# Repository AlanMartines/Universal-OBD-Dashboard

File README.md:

# Universal-OBD-Dashboard

Desenvolvido por **Alan Martines** · mantido pela **[Eletro Info Tecnologia](https://www.eletroinfotecnologia.com.br/)**.
<br clear="left">

Universal-OBD-Dashboard é uma plataforma de telemetria automotiva de código aberto projetada para Android e Android Auto. O projeto utiliza adaptadores OBD2 (Bluetooth SPP / chip duplo PIC18F25K80) para coletar, calcular e exibir dados do veículo com alta fidelidade, funcionando de forma 100% agnóstica via arquivos de perfil JSON.

*English summary: [README.en.md](README.en.md).*

Os seis temas do painel no modo noite, em cada aba do rodapé (dados do simulador):

| Tema | Estrada | Motor | Viagem | Dinâmica |
|---|---|---|---|---|
| **Minimal** |  |  |  |  |
| **Cápsula** |  |  |  |  |
| **HUD** |  |  |  |  |
| **Pista** |  |  |  |  |
| **Clássico** |  |  |  |  |
| **Horizonte** |  |  |  |  |

## Destaques
- **Compatibilidade com Android Auto**: Interface nativa baseada na AndroidX Car App Library. Instalado por APK, o app não aparece no carro a partir do Android Auto 17.7 ([detalhes](docs/android-auto.md#no-carro-apk-fora-da-play-store)).
- **Motor em Segundo Plano**: Coleta ininterrupta de dados e diagnóstico com tela do celular bloqueada (Foreground Service).
- **Caixa Preta de Viagens**: Registro contínuo em banco de dados SQLite local (Trip Computer e logs de DTCs).
- **Perfis Customizáveis**: Configure fórmulas, limites de RPM/temperatura e PIDs específicos por montadora sem alterar o código-fonte.
- **Perfil Uno Vivace Incluso**: Mapeamento completo para Fiat Uno Vivace 1.0 Flex (ECU Magneti Marelli IAW 7GF).

## Hardware Recomendado
- Adaptador OBD2 Bluetooth (SPP) compatível com ELM327, inclusive os clones "v1.5" com PIC18F25K80, usados no desenvolvimento. Adaptadores com chip STN (OBDLink) também funcionam. *Ajustes → Console da rede → Identificar adaptador* mostra o que é o seu.
- Dispositivo Android 8.0+ compatível com Android Auto.
- O app **só faz consultas** ao carro: leituras do modo 01, códigos de falha, identificação e comandos do próprio adaptador. Nada é escrito na ECU.

## Arquitetura

```
 ┌──────────── ObdForegroundService (FGS connectedDevice|location + Partial WakeLock) ────────────┐
 │                                                                                                 │
 │  BluetoothSerialManager ──► CommandQueue (EDF, 1 comando em voo) ──► TelemetryHub (StateFlow)   │
 │        SPP/RFCOMM             alta 100 ms │ média 1,5 s │ sentinela 10 s        │               │
 │                                                                                 ▼               │
 │  GPS (Google ou nativo) ────────────────────────────────────────────► TelemetryEngine (250 ms) │
 │                                                    consumo · marcha · alertas · energia         │
 │                                                                                 │               │
 │                                                     Room: trips · telemetry_log (2 s) · DTCs    │
 └─────────────────────────────────────────────────────────────────────────────────────────────────┘
          ▲ AutoDisconnectReceiver (ACL)       TelemetryHub ──► TelemetryScreen (Android Auto)
          ▲ DashboardSession (Android Auto)                └──► MainActivity (WebView assets/web)
```

| Pacote | Arquivo | Responsabilidade |
|---|---|---|
| `obd` | `ProfileParser.kt` | Modelo do perfil JSON, validação e **avaliador de fórmulas** (compila para AST uma vez) |
| `obd` | `ElmProtocol.kt` | Parser de respostas ELM327 (single/multi-frame ISO-TP, erros) e decodificador de DTC |
| `obd` | `CommandQueue.kt` | Escalonador das três esteiras sobre o socket SPP |
| `obd` | `BluetoothSerialManager.kt` | Socket RFCOMM, leitura até o prompt `>` e timeouts |
| `telemetry` | `TelemetryHub.kt` / `TelemetryEngine.kt` | Estado compartilhado, consumo, indicador de marcha, alertas, acumulador de viagem |
| `service` | `ObdForegroundService.kt` | Ciclo de vida, reconexão, GPS, máquina de estados de energia, gravação Room |
| `service` | `AutoDisconnectReceiver.kt` | Início/fim automáticos por eventos Bluetooth |
| `car` | `DashboardCarAppService.kt` / `TelemetryScreen.kt` | Android Auto (`GridTemplate`) |
| `db` | `AppDatabase.kt` / `TripDao.kt` / `TelemetryEntity.kt` | Caixa preta SQLite (viagens, telemetria, falhas, abastecimentos, respostas da IA) |
| `bridge` | `AppBridge.kt`, `HistoryBridge.kt`, `FuelBridge.kt`, `DiagnosticsBridge.kt`, `AiBridge.kt` | Pontes JavaScript da tela, uma por assunto (contrato conferido por `BridgeContractTest`) |
| `fuel` | `FuelLog.kt` / `FuelCalibration.kt` | Consumo real entre tanques cheios, mistura etanol/gasolina, calibração |
| `ai` | `AiClient.kt`, `DtcPrompt.kt`, `TripDigest.kt`, `HistoryContext.kt` | Assistente IA opcional (só agregados saem do celular) |
| `backup` | `BackupArchive.kt` / `BackupManager.kt` | Backup completo (.zip) e restauração |
| `diagnostics` | `CanListener.kt`, `AdapterIdentify.kt`, `DiagnosticRecorder.kt` | Console da rede, identificação do adaptador e gravação de diagnóstico |

A tela (`assets/web`) é dividida em `app-core.js` (ponte e utilitários) … `app-main.js` (inicialização), carregados em ordem pelo `index.html`; `WebAssetsTest` confere ids e nomes repetidos.

### Escalonador (CommandQueue)

Cada comando tem `próximo_envio = último_envio + intervalo_da_esteira`. A cada iteração é enviado o comando vencido com o prazo mais antigo (*Earliest-Deadline-First*); empates favorecem a esteira de maior prioridade. Nunca há escrita antes do prompt `>` da resposta anterior, o que evita o `BUFFER FULL` do ELM327.

Um ELM327 via SPP responde tipicamente 10–25 requisições/s. Com 4 PIDs a cada 100 ms (40 req/s) a esteira de alta frequência roda "o mais rápido possível" e o EDF garante que média e sentinela não sofram inanição. Otimizações incluídas:

- `ATS0` (sem espaços) e sufixo de contagem de respostas (`010C1`, `append_response_count`), que faz o ELM devolver sem esperar o timeout;
- descoberta de PIDs suportados (`0100/0120/…`): PIDs ausentes são desativados ou trocados pelo `fallback_command` (ex.: tensão `0142` → `ATRV`);
- modo ocioso: com o veículo parado, as esteiras são desaceleradas (`idle_poll_multiplier`).

### Gerenciamento de energia

| Evento | Ação |
|---|---|
| ACL do adaptador/dispositivo-gatilho conecta | inicia o serviço |
| Sessão do Android Auto criada | inicia o serviço |
| Bluetooth cai e não reconecta (`reconnect_attempts`, padrão 6) | salva a viagem e encerra |
| Adaptador responde mas a ECU não (ignição ainda desligada) | espera até `ignition_wait_s` (5 min) antes de encerrar |
| ECU sem resposta por `ecu_silence_timeout_s` (ignição desligada com adaptador ainda energizado) | salva a viagem e encerra |
| OBD **e** GPS ≤ limiar pelo tempo de *Ajustes → Captura* (5, 15 ou 30 min, ou nunca; padrão 15) | notificação "Continuar / Encerrar" (também no Android Auto); polling e GPS em baixa potência |
| Sem resposta em `idle_confirm_timeout_s` | salva a viagem e encerra |

> **Adaptadores ELM327 são passivos**: o evento `ACL_CONNECTED` só ocorre quando o telefone abre o socket. Para início 100% automático, cadastre em *Ajustes → Dispositivos-gatilho* o nome Bluetooth da multimídia do carro ou use o Android Auto. No Android 12+ o sistema pode bloquear o início a partir de segundo plano; nesse caso aparece uma notificação "Toque para iniciar".

### Exportação de viagens

Na aba *Histórico*, cada viagem tem os botões **CSV** e **GPX**, que abrem o menu de compartilhamento do Android (Drive, e-mail, WhatsApp...).

| Formato | Conteúdo |
|---|---|
| CSV | Uma linha por amostra da caixa preta (2 s): `timestamp_ms`, `time_utc`, colunas fixas (rpm, velocidade OBD/GPS, TPS, MAP, temperaturas, tensão, trims, lambda, consumo, GPS) e uma coluna para cada saída extra do perfil. Vírgula como separador e ponto decimal. |
| GPX 1.1 | Trajeto com `<trkpt>` por amostra com GPS (novo segmento após 30 s sem fix), extensões `obd:speed_kmh`, `obd:rpm`, `obd:coolant_c`, `obd:throttle_pct` e `obd:fuel_lph`, e um `<wpt>` por falha (DTC) com o freeze frame. Abre no Google Earth, Strava, OsmAnd etc. |

O código fica em `export/TripExporter.kt` (Kotlin puro, testado na JVM) e `export/TripExportFiles.kt` (arquivo em `cache/exports`, apagado após 24 h).

### Gravação de diagnóstico

Para testes em veículos novos e para calibração, ative *Ajustes → Gravação de diagnóstico*. A partir da próxima captura, cada sessão gera um arquivo `diag_<data>_<perfil>.jsonl`, com uma linha JSON por evento:

| `type` | Conteúdo |
|---|---|
| `session` | versão do app, perfil, celular/Android, nomes do adaptador |
| `adapter` | versão do ELM, PIDs suportados e desativados |
| `elm` | `cmd`, resposta bruta `rx` (ou `err`), latência `ms` |
| `scan` | início/fim da varredura única da ECU (respostas nas linhas `elm`) |
| `snapshot` | 1×/s: leituras, métricas derivadas, GPS, estado de conexão/energia |
| `status`, `power`, `alert`, `dtcs`, `pid_status`, `error`, `stop` | eventos da sessão |

Em *Ajustes*, cada arquivo tem **Exportar .gz** (menu de compartilhar). Falhas fatais do app ficam em `crash_<data>.txt` na mesma lista. Ocupa cerca de 5–10 MB por hora (bem menos compactado).

### Assistente IA (opcional)

*Ajustes → Assistente IA* liga um botão **Explicar com IA** em cada código de falha, nas falhas ativas e no histórico. O app manda à IA o veículo, o motor/ECU, o código, a descrição do perfil e as leituras do momento da falha (rotação, velocidade, carga, temperatura), e mostra a resposta: significado, causas prováveis, gravidade e o que verificar.

- **Provedores:** qualquer API no formato OpenAI (`POST <endereço>/chat/completions`, chave em `Authorization: Bearer`).

  | Provedor | Endereço |
  |---|---|
  | OpenAI | `https://api.openai.com/v1/` |
  | Claude | `https://api.anthropic.com/v1/` |
  | Gemini | `https://generativelanguage.googleapis.com/v1beta/openai/` |
  | Personalizado | outro endereço `https://` (OpenRouter, Groq…) |

  Com a chave colada, **Atualizar modelos** busca na conta do provedor os modelos de texto que ela pode usar (`GET <endereço>/models`; na Claude, com os cabeçalhos `x-api-key` e `anthropic-version` da Anthropic). É só escolher na lista. O nome também pode ser digitado.
- **Privacidade:**
  - Nunca saem GPS, trajeto, horário, VIN nem o número da viagem. O lado nativo só aceita uma lista fechada de campos, e um teste garante isso.
  - Antes do primeiro envio, o app mostra o texto exato que vai sair. Depois disso, ele continua disponível em "O que foi enviado".
- **Analisar viagem:** o botão **Analisar com IA** de cada viagem envia um resumo calculado no celular, sem coordenadas, horário nem VIN. O resumo traz:
  - distância, tempos em movimento e parado;
  - faixas de velocidade e rotação e o tempo em cada marcha estimada;
  - consumo em até 8 trechos;
  - temperaturas, tensão e falhas.
- **Perguntar à IA** (aba Histórico): conversa sobre o carro. O contexto é montado no celular:
  - as 40 viagens mais recentes, com data sem horário;
  - os abastecimentos, sem nome do posto nem observações;
  - consumo real, gastos por mês e o ponto de equilíbrio etanol × gasolina;
  - as falhas registradas.
- **Confirmação:** antes do primeiro envio de cada tipo (falha, viagem, pergunta), o app mostra o texto e espera o **Enviar**.
- **Chave de API:**
  - Cifrada com AES-GCM, com a chave no Android Keystore do aparelho.
  - Aparece mascarada e não entra em exportações.
  - Em outro celular, um backup não a revela.
- **Custo e rede:** cada consulta usa créditos da sua conta no provedor. Sem internet, o botão avisa e o resto do app funciona igual.

### Telemetria remota (opcional)

*Ajustes → Telemetria remota* envia as leituras para um servidor próprio ([server/](server/README.md)). Fica desligada até você parear.

- **Pareamento:** no painel, crie o dispositivo e use o código de uso único no app. O app gera um identificador aleatório e não usa IMEI nem MAC.
- **O que sai:** só as leituras dos sensores, o horário, o número da viagem e os códigos de falha ativos. VIN não é enviado. O GPS tem opção própria, desligada por padrão.
- **Só de saída:** a resposta do servidor nunca vira comando para o adaptador ou o carro.
- **Sem sinal:** a telemetria continua na caixa preta do celular e sobe depois. O histórico anterior ao pareamento não é enviado.
- **Quando envia:** durante a captura, ou ao tocar em *Enviar agora*.
- **Painel do veículo:** durante a captura, o app também manda a última leitura para o painel web: uma por segundo com alguém olhando e uma a cada 10 s sem ninguém, para economizar dados. Essa leitura não fica guardada.
- **Segurança:** apenas `https://`, sem seguir redirecionamentos. O token fica cifrado no Android Keystore.

### Console da rede (escuta CAN)

*Ajustes → Console da rede* abre uma tela tipo terminal que escuta por 60 s o tráfego CAN dos pinos 6/14, somente ouvindo: o ELM327 fica em modo silencioso (`ATCSM1`) e só recebe comandos `AT`. Se o adaptador não aceitar o modo silencioso, a escuta é cancelada. Com *Velocidade: automática*, o app experimenta 500, 250, 125, 100, 83,3, 50 e 33,3 kbps por 4 s cada e escuta na que trouxe mais quadros. No fim, mostra um resumo por ID com os bytes que variaram.

**Identificar adaptador** (no mesmo console) envia só comandos internos do adaptador, nunca ao carro: `ATZ`, `ATI`, `AT@1`, `AT@2`, `ATPPS`, `ATCSM1`, `STI` e `ATRV`. Com as respostas, o app aponta clone de ELM327, chip STN (OBDLink) ou "nenhum sinal de clone". Um adaptador é clone quando declara uma versão que a Elm Electronics nunca lançou (como a v1.5) ou quando diz ser v1.4 ou mais nova sem conhecer `ATCSM`/`ATPPS`. O resultado fica em `diag_<data>_console-identificar.jsonl`.

Cada escuta gera `diag_<data>_console-escuta.jsonl`, com linhas `can` (`l` = quadro bruto, `ms` desde o início), `can_probe`, `can_summary` e `elm`. O arquivo aparece no histórico do console e na lista de arquivos de diagnóstico, com as opções ver, exportar .gz e apagar. Use com a captura encerrada e a ignição ligada.

Se o adaptador for um clone sem `ATCSM`, como o usado no desenvolvimento, a escuta pode ser feita fora do app com um Arduino Uno + MCP2515 em modo Listen-Only, que garante no hardware que nada é transmitido: veja [docs/can-escuta.md](docs/can-escuta.md).

### Continuidade da viagem

Depois de uma **desconexão automática** (ignição desligada, queda de Bluetooth, inatividade sem resposta, app reiniciado pelo sistema), uma captura que começa até **1 hora** depois (ajustável em *Ajustes → Captura*) **continua a mesma viagem**: mesmos totais no histórico, mesmo CSV/GPX e mesmo arquivo de diagnóstico (com um evento `resume`). Encerrar à mão (*Encerrar viagem* no app, na notificação ou no Android Auto, ou *Encerrar agora* na inatividade) faz a próxima captura começar uma viagem nova. A varredura de diagnóstico da ECU roda uma vez por dia por veículo, e *Ajustes → Pronto para viajar* lista as permissões e ajustes de bateria que mantêm a captura e o GPS em segundo plano.

### Painel de instrumentos

A aba **Painel** mostra os instrumentos em seis temas, trocados pelo botão no rodapé do painel: **Minimal** (barra de RPM no topo, marcha e velocidade grandes), **Cápsula** (velocímetro e conta-giros de arco na cor escolhida, verde ou vermelho, cápsula central com luzes, barras de combustível/temperatura e células), **HUD** (moldura neon com escalas na borda e estrada animada pela velocidade), **Pista** (conta-giros em setores com a marcha no miolo e luzes de troca), **Clássico** (dois mostradores redondos com aro metálico e ponteiro) e **Horizonte** (arco largo de RPM com a velocidade no centro). Cada tema tem modo dia/noite (automático pelo tema do Android ou pelo horário) e três telas de seis campos (**Estrada**, **Motor**, **Viagem**), trocadas por toque, por deslize ou sozinhas (Viagem quando o carro para). A quarta aba, **Dinâmica**, ocupa a tela toda com o câmbio (P parado, D andando, R de ré), o inclinômetro lateral e frontal, a força G, a bússola com o horizonte, a curva (direção e giro) e o ambiente (altitude e pressão); usa o LSM6DS3 e o magnetômetro da placa do ESP32, cruzados com o GPS do celular (parado, o rumo vem do magnetômetro do ESP32, da bússola do próprio celular ou da média das duas quando concordam), e tem os botões **Zerar nível** e **Calibrar frente**. Limites, faixas térmicas, relações de marcha e papéis vêm do perfil JSON, então o painel serve para qualquer veículo.

Com o celular **na horizontal** e o Painel aberto, o app entra em tela cheia; durante a captura, com o Painel aberto, a tela fica ligada. O painel anterior, com todos os sensores, alertas e falhas em lista, continua na aba **Detalhes**. Para avaliar os temas fora do app (simulador ou trecho de viagem real), veja [tools/painel-preview](tools/painel-preview/README.md).

### Detalhes: falhas e monitores de prontidão

A aba **Detalhes** mostra as falhas ativas e os **monitores de prontidão** da ECU: os autodiagnósticos que ela roda sozinha ao dirigir (catalisador, sonda, sistema de combustível, falha de ignição…), vindos dos bytes B–D do PID `0101`. "Em teste" é normal depois de desligar a bateria ou apagar códigos.

Quando surge uma falha nova, o app lê uma vez o **congelamento de quadro gravado pela própria ECU** (modo 02). O resultado aparece no histórico de falhas e entra no "Explicar com IA".

### Abastecimentos

A aba **Abastecimentos** registra cada parada no posto: data e hora, hodômetro, litros, valor pago (ou preço por litro), combustível (gasolina, aditivada/premium, etanol ou mistura), se foi tanque cheio e o posto. Com dois **tanques cheios** com hodômetro, o app mostra o **consumo real** (litros colocados ÷ km rodados), o **custo por km**, o **gasto do mês** e, para cada intervalo, quanto o próprio app tinha estimado, como conferência da calibração. Com tanques cheios de etanol e de gasolina, mostra a partir de que preço o **etanol compensa neste carro**. Registrar um tanque cheio na hora também acerta o nível do tanque e o hodômetro do app.

O card **Calibração do consumo** compara, em cada intervalo entre tanques cheios, os litros reais com o que o app estimou. A estimativa é a integral do consumo gravado no período. Com 3 ou mais intervalos parecidos, o card sugere um fator de correção, que se aplica com um toque e vale por veículo. Intervalos com diferença acima de 25% ficam de fora, por exemplo tanque não completado ou % de etanol errado.

**Etanol da bomba no tanque** (em Ajustes) é só a parte do tanque que veio da bomba de etanol: 0% = só gasolina. O etanol anidro que a lei manda misturar na gasolina (32% na comum e aditivada desde agosto de 2026; 25% na premium) já está no combustível "gasolina" do perfil e não deve ser somado ali.

**Exportar CSV** compartilha todos os abastecimentos (`data_hora,hodometro_km,litros,valor_total,preco_litro,combustivel,etanol_pct,tanque_cheio,posto,observacao`); o mesmo formato pode ser importado de um arquivo (**Escolher arquivo .csv**) ou colado em **Importar**, com a opção de substituir todos os registros.

### Backup completo

*Ajustes → Backup completo* gera um `.zip` com o banco (viagens, telemetria, falhas, abastecimentos, respostas da IA), os ajustes e os perfis importados, para guardar ou levar para outro celular. **Restaurar backup** substitui tudo pelo conteúdo do arquivo, migrando o banco se o backup for de uma versão anterior, e recusa backups de versões mais novas. A chave de API da IA não entra no backup. Com esse CSV, `tools/trip-report --fuel-csv` calibra o consumo intervalo a intervalo.

## Perfis JSON

Passo a passo para criar o perfil de outro carro: [docs/criar-perfil.md](docs/criar-perfil.md).

Perfis embarcados ficam em `app/src/main/assets/profiles/`. Perfis importados pela tela *Ajustes* são gravados em `<filesDir>/profiles/` e têm precedência sobre os embarcados com o mesmo `profile_id`.

| Seção | Descrição |
|---|---|
| `init_commands` | Sequência AT enviada após conectar |
| `adapter` | Nomes Bluetooth, timeouts, `append_response_count`, `query_supported_pids` |
| `lanes` | `interval_ms`, `priority` e `throttle_when_idle` de cada esteira |
| `pids.<esteira>[]` | `command`, `formula` (bytes `A`..`Z`) **ou** `outputs[]` (com `hidden` para valores internos), `decoder` (`formula`/`dtc`/`elm_voltage`), `fallback_*` |
| `roles` | Associa papéis semânticos (rpm, speed, map, coolant_temp…) aos ids do perfil |
| `alerts[]` | `condition` (expressão sobre os ids), `level`, `message` com `{id}`, `sustain_ms`, `notify` |
| `thermal`, `dashboard` | Faixas térmicas e limites dos mostradores |
| `fuel` | Tanque, reserva, método (`speed_density`/`maf`), cilindrada, VE, combustíveis flex, corte em desaceleração |
| `shift_indicator` | Velocidades de troca econômica e, opcionalmente, km/h por 1000 RPM de cada marcha |
| `power_management` | Tempos de inatividade, silêncio da ECU e reconexão |

**Fórmulas e condições** aceitam `+ - * / %`, `& | ^ << >>`, comparações, `&& || !`, ternário `c ? a : b` e as funções `min max abs round floor ceil sqrt clamp signed8 signed16`. Nas condições de alerta também estão disponíveis `gps_speed`, `fuel_lph`, `fuel_kml`, `fuel_remaining_l`, `trip_distance_km`, `dtc_confirmed_count` e `dtc_pending_count`. Valor ausente vale `NaN`, então a condição é falsa e não há alerta com dado faltando.

### Perfil Fiat Uno Vivace (IAW 7GF)

É o primeiro carro mapeado, não uma regra para os demais. Cada veículo tem a sua pasta em [veiculos/](veiculos/README.md), e a ligação com ESP32 é específica de cada um.

- ISO 14230-4 KWP FAST pela linha K (pino 7), confirmado em viagem; `ATSP5` fixa esse protocolo, sem busca automática que transmitiria na CAN da carroceria; RPM 0–7000 com redline em 6250 RPM e marcha lenta de 815 ± 50 RPM;
- termostato 87 °C, eletroventilador 1ª 97 °C / 2ª 103 °C, crítico > 105 °C;
- troca econômica 1→2 aos 14,8 km/h, 2→3 aos 28,2, 3→4 aos 43,8 e 4→5 aos 61,4 km/h;
- tanque de 48 L, reserva entre 5,5 e 7,5 L (nível estimado por integração do consumo a partir do último "Tanque cheio");
- consumo por *speed-density* (a 7GF não tem MAF), com `volumetric_efficiency` 0,99 calibrada em três abastecimentos reais (consumo medido de 12,5–13,2 km/l na estrada com gasolina).

A luz **STOP** (pressão de óleo) do quadro é ligada direto ao pressostato e não é exposta via OBD. Especificações completas em [veiculos/fiat-uno-vivace-2012](veiculos/fiat-uno-vivace-2012/).

## Compilação

1. Android Studio com suporte ao AGP 9 (2026 ou mais recente), com o JDK 17 ou mais novo.
2. Abra a pasta do projeto; o Studio usa o Gradle do wrapper (9.x). O build é em Kotlin DSL (`*.gradle.kts`), com as versões em `gradle/libs.versions.toml`, e compila com o SDK 37 (`targetSdk` 36).
3. Pela linha de comando: `./gradlew :app:assembleDebug` gera `app/build/outputs/apk/debug/app-debug.apk` (requer `ANDROID_HOME` ou `sdk.dir` em `local.properties`).
4. Testes de unidade do núcleo (fórmulas, parser ELM, DTC, perfis): `./gradlew :app:testDebugUnitTest`.
   Inclui o **simulador de ELM327 em JVM** (`app/src/test/java/.../obd/sim/Elm327Simulator.kt`), que exercita a `CommandQueue` com os perfis reais, em tempo virtual, sem adaptador nem carro: protocolos CAN e K-Line, DTCs, ignição desligada, adaptador travado e clones limitados.

### Testar no Android Auto

O app usa a categoria `androidx.car.app.category.IOT`, porque não existe categoria de telemetria.

> **Limite do APK no carro:** a partir do Android Auto 17.7, a opção *Fontes desconhecidas* não libera mais apps da Car App Library instalados por APK. O app fica fora da lista do carro, mesmo com a opção ligada. Hoje, o Android Auto instalado por APK só funciona no simulador *Desktop Head Unit* (DHU) do computador. Detalhes e saídas em [docs/android-auto.md](docs/android-auto.md#no-carro-apk-fora-da-play-store).

O teste no DHU e o que conferir estão em [docs/android-auto.md](docs/android-auto.md). A tela também é testada automaticamente (`TelemetryScreenTest`).

### Integração contínua

Todo push no `master` e todo PR rodam no GitHub Actions ([ci.yml](.github/workflows/ci.yml)):
- `testDebugUnitTest`, `lintDebug` e `assembleDebug`. Os testes incluem Robolectric para a migração do banco, o backup e o Android Auto.
- Os testes das ferramentas `tools/trip-report` (inclusive a paridade do cálculo de consumo com o app) e `tools/can-capture`.
- O job **smoke**, que instala num emulador o APK otimizado pelo R8 (variante `smoke`: release com a chave de debug) e confere que o app abre sem travar.
- O job **servidor**, com os testes da `api` e do `web` contra um PostgreSQL descartável.
- O job **seguranca**:
  - procura segredos em todo o histórico com o gitleaks; os falsos positivos conferidos ficam no [.gitleaksignore](.gitleaksignore);
  - procura falhas conhecidas (altas e críticas, com correção disponível) nas dependências, nos Dockerfiles e nas imagens do painel com o Trivy.

O fluxo só tem permissão de leitura no repositório. As Actions são presas pelo hash do commit, e as ferramentas de segurança rodam pelas imagens oficiais presas por digest.

O Dependabot ([dependabot.yml](.github/dependabot.yml)) avisa toda semana sobre atualizações do Gradle, das Actions, do npm do painel e da imagem base do Node. O APK de debug e os relatórios de teste/lint ficam disponíveis como artefatos da execução.

O APK de debug é assinado com a chave fixa `app/debug.keystore` (versionada de propósito; senha `android`). Assim, APKs gerados pelo CI ou por qualquer máquina atualizam uns aos outros sem precisar desinstalar o app, o que apagaria viagens e ajustes.

### Releases

Ao enviar uma tag `vX.Y.Z`, o workflow [release.yml](.github/workflows/release.yml) roda os testes, gera o APK **assinado com a chave de release** e publica em *Releases* com as notas da seção `## [X.Y.Z]` do CHANGELOG. Tags `v0.*` saem como *pre-release*.

**Configuração (uma vez):**
1. No seu computador, rode `scripts/criar-chave-release.sh`. Ele cria `~/.android-keys/universal-obd-release.jks` (fora do repositório) e um `.base64.txt` dela.
2. Em *Settings → Secrets and variables → Actions*, cadastre `RELEASE_KEYSTORE_BASE64`, `RELEASE_STORE_PASSWORD`, `RELEASE_KEY_PASSWORD` e `RELEASE_KEY_ALIAS` (o script mostra os valores).
3. Apague o `.base64.txt` e faça **backup da chave e da senha**: sem elas não é possível publicar atualizações para quem já instalou o app.

**Publicar uma versão:**
1. No CHANGELOG, mova o conteúdo de `[Não lançado]` para `## [X.Y.Z] - AAAA-MM-DD` e atualize os links do rodapé.
2. Em `app/build.gradle.kts`, ajuste `versionName = "X.Y.Z"` e incremente `versionCode`.
3. Commit (`chore: versão X.Y.Z`), depois `git tag vX.Y.Z` e `git push origin master vX.Y.Z`.

O workflow falha com uma mensagem clara se a tag não bater com `versionName`, se a seção do CHANGELOG não existir ou se os secrets não estiverem configurados.

Para assinar um release localmente, defina as mesmas variáveis (`RELEASE_STORE_FILE`, `RELEASE_STORE_PASSWORD`, `RELEASE_KEY_ALIAS`, `RELEASE_KEY_PASSWORD`) no ambiente ou em `~/.gradle/gradle.properties` e rode `./gradlew :app:assembleRelease`. Sem elas o Gradle gera `app-release-unsigned.apk`.

> O APK de release usa outra chave, então não atualiza um APK de debug instalado (nem o contrário): troque de um para o outro desinstalando antes.

## Versionamento

O projeto segue o [Versionamento Semântico](https://semver.org/lang/pt-BR/) (`MAJOR.MINOR.PATCH`) e as mudanças de cada versão ficam no [CHANGELOG.md](CHANGELOG.md).

- **MAJOR**: mudança incompatível no formato dos perfis JSON (`schema_version`) ou no banco Room sem migração.
- **MINOR**: novas funcionalidades, PIDs, perfis de veículo ou telas compatíveis.
- **PATCH**: correções de bugs e ajustes de calibração.

As tags usam o prefixo `v` (ex.: `v0.1.0`) e devem coincidir com `versionName` em `app/build.gradle.kts`. Enquanto a versão for `0.x`, o formato dos perfis ainda pode mudar.

Versão atual: **0.4.0**.

## Como contribuir

Relatos de problema, perfis de outros carros e pull requests são bem-vindos. As regras (somente consulta ao carro, cuidado com dados pessoais) e o passo a passo estão em [CONTRIBUTING.md](CONTRIBUTING.md).

## Licença
O código é distribuído sob a [licença MIT](LICENSE).

O nome **Eletro Info Tecnologia**, a logo e o emblema `[EI]` (ícone do app) são marcas da Eletro Info Tecnologia e **não** fazem parte da licença MIT. Quem publicar uma versão modificada do app deve usar outro nome e outro ícone.

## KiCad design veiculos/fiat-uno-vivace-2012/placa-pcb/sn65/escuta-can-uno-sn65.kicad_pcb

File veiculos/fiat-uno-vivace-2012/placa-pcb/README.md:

# PCB da escuta CAN (KiCad 9)

PCB de duas faces para fábrica (JLCPCB, PCBWay), com o **mesmo circuito** da placa ilhada 5 × 7 cm na versão
**TJA1050** (`../placa/`). Tudo sai do `gerar_kicad.py`, sem interface gráfica:

```bash
python3 veiculos/fiat-uno-vivace-2012/placa-pcb/gerar_kicad.py
```

O script lê as posições e as ligações do `../placa/gerar_placa.py`, as alturas dos módulos do `../placa/gerar_3d.py`
e o tamanho da placa e dos apoios do `../placa/caixa.py`. Mudou a placa ilhada, rode de novo.

## O que ele gera

| Arquivo | Conteúdo |
|---|---|
| `escuta_can.kicad_sym`, `escuta_can.pretty/`, `escuta_can.3dshapes/` | Biblioteca do projeto: ESP32 DevKit V1 (50 × 28 mm, barras a 25,4 mm), TJA1050 (22 × 11 mm), RT8272 HW-108 (21 × 21 mm), porta-fusível AS-06 (pinos a 20,32 mm, furo de 1,5 mm), ilhas do cabo OBD, barras, resistores, C1 e pontos de teste Keystone 5000. Modelos 3D: a placa de cada módulo com as medidas reais (VRML e STEP próprios) e, por cima, os componentes com os modelos oficiais da KiCad (ESP32-WROOM-32, micro-USB Molex, SO-8, bobina, trimpot, SMD 0805 e 1206), nos lugares das peças reais |
| `escuta-can-uno.kicad_pro`, `.kicad_sch`, `.kicad_pcb`, `.kicad_dru` | Projeto KiCad. Regras: sinal ≥ 0,25 mm, alimentação (12 V, 12 V com fusível, 5 V, 3V3, GND) ≥ 0,6 mm, folga ≥ 0,2 mm |
| `fabricacao/gerbers-escuta-can-uno.zip` | 9 Gerber, furação Excellon (PTH e NPTH) com mapa e o job: é o que vai para a fábrica |
| `fabricacao/BOM.csv`, `fabricacao/CPL.csv` | Lista de peças e posições no formato da JLCPCB (centro de cada peça, origem no canto de baixo à esquerda) |
| `fabricacao/esquematico.pdf`, `pcb-top.svg`, `pcb-bottom.svg` | Revisão 2D (a face de baixo vem espelhada, como se vê virando a placa) |
| `fabricacao/escuta-can-uno.step`, `render-3d-top.png`, `render-3d-bottom.png` | Modelo 3D (STEP AP214) e as duas vistas, com as peças |
| `fabricacao/render-3d-top-sem-componentes.png`, `render-3d-bottom-sem-componentes.png` | As duas vistas da PCB sem componentes (só a placa) |

O script roda o ERC e o DRC (com a conferência entre esquemático e placa) e para se sobrar qualquer violação ou
ligação faltando. Só depois exporta.

## Versão SN65HVD230

```bash
PCB_VARIANTE=sn65 python3 veiculos/fiat-uno-vivace-2012/placa-pcb/gerar_kicad.py
```

Gera o mesmo conjunto em [`sn65/`](sn65/) (projeto `escuta-can-uno-sn65`, `sn65/fabricacao/gerbers-escuta-can-uno-sn65.zip`
etc.), a partir da placa ilhada dessa versão:

- **Sem R1, R2, R3 e J2:** o CRX vai direto ao D21.
- **CTX preso no 3V3:** o 3V3 chega ao módulo por baixo.
- **R4 na coluna 18:** o CANH desce por cima pela coluna 18.

O resto (alimentação, sensores, bateria, LED, pontos de teste, regras e encomenda) é igual. ERC, DRC e paridade zerados.

## Como a placa está feita

- **Placa:** 50 × 70 mm, 2 camadas, 1,6 mm. Os 4 cantos (3,5 × 3,5 mm, onde a caixa apoia a placa) ficam sem cobre.
- **Face de cima:** a alimentação (12 V do OBD com 1,0 mm; 12 V com fusível e 5 V com 0,8 mm; ramais e 3V3 com 0,6 mm),
  o RX do TJA1050, o divisor do RX e o LED.
- **Face de baixo:** plano de GND na placa toda e os sinais que cruzam a alimentação (SDA, SCL, D34 e CANH), com 0,3 mm.
- **Plano de GND:** também na face de cima, nos espaços livres, costurado com 120 vias de 0,6/0,3 mm.
- **Só escuta:** o TXD do TJA1050 fica preso em 5 V, então o transceptor nunca transmite. O CANH fica em 3,3 V pelo R4
  e o CANL vai ao pino 14 do OBD (o pino 6 fica sem ligação).

Diferenças de posição em relação à placa ilhada (o circuito é o mesmo):

- **C1:** desce para a linha 20, para não encostar no R6.
- **R5:** sobe uma linha (17 a 21), para não encostar no porta-fusível.
- **TP3:** vai para o furo (10, 16), porque a trilha do 5 V passa na linha 13.

Os módulos, o porta-fusível, as barras dos sensores, o LED e o cabo OBD ficam nos mesmos furos: a placa cabe na
mesma caixa.

## Encomenda (referência: [PCB Brasil](https://pcbbrasil.com.br/quote))

| Opção | Valor |
|---|---|
| Dimensões | 50 × 70 mm |
| Quantidade | 5 |
| Layers | 2 |
| Material | FR-4, TG 150-160 |
| Espessura | 1,6 mm (a caixa conta com ela) |
| Menor pista/distância | 6/6 mil (a folga mínima do projeto é 0,2 mm, menos que 8 mil) |
| Menor furo | 0,3 mm (vias de costura) |
| Máscara / silkscreen | verde / branco |
| Gold fingers | não |
| Acabamento | HASL (com ou sem chumbo) |
| Vias | tenting |
| Cobre | 1 oz |
| Stencil e montagem | não (peças de furo, soldadas à mão) |

Arquivo: `fabricacao/gerbers-escuta-can-uno.zip`.

## Antes de mandar fabricar

1. **Medidas reais:** confira os módulos nas barras, encaixando o ESP32, o TJA1050 e o RT8272 sobre o desenho em
   tamanho real (`pcb-top.svg` impresso em 100 %).
2. **Peças da montagem:** a CPL e a BOM servem para a montagem pela fábrica, mas todas as peças são de furo
   (montagem à mão). Na JLCPCB, peça só a placa.
3. **Fios do cabo OBD:** confira as cores com o multímetro antes de soldar (a tabela está em `../placa/README.md`).

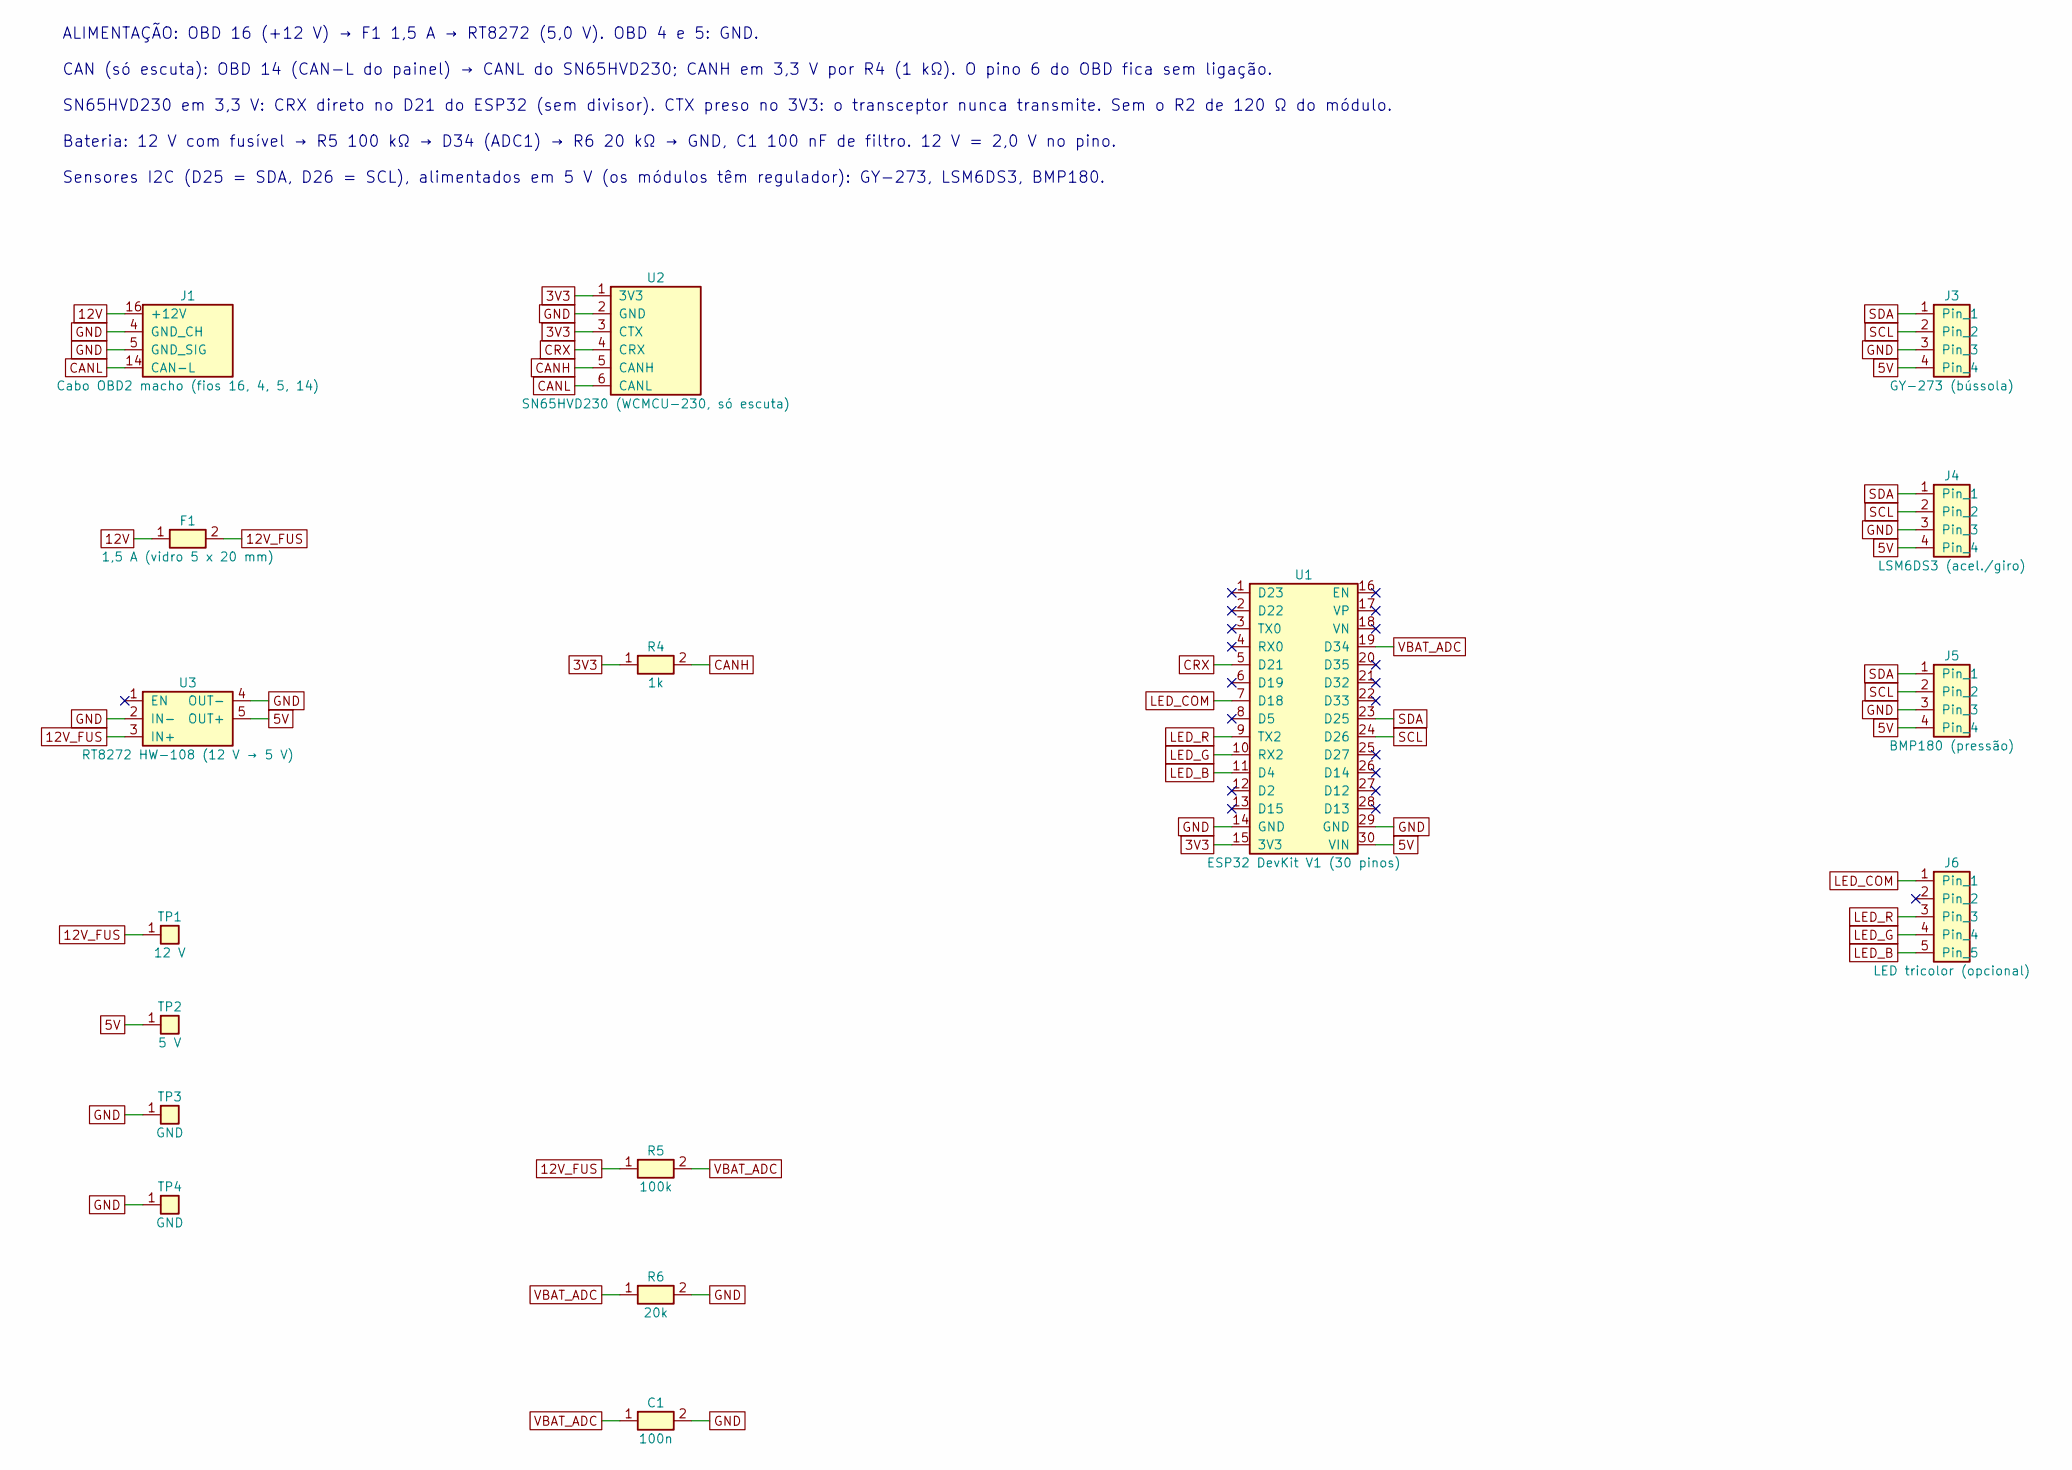
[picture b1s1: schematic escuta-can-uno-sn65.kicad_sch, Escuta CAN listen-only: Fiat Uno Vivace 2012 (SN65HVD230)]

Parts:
C1: 100n; C_Disc_D5.0mm_P5.08mm
F1: 1,5 A (vidro 5 x 20 mm); Fuseholder_AS06_5x20_P20.32
J1: Cabo OBD2 macho (fios 16, 4, 5, 14); OBD_Pigtail_4W
J3: GY-273 (bússola); PinHeader_1x04_H
J4: LSM6DS3 (acel./giro); PinHeader_1x04_H
J5: BMP180 (pressão); PinHeader_1x04_H
J6: LED tricolor (opcional); PinHeader_1x05_H
R4: 1k; R_Axial_DIN0207_P10.16mm
R5: 100k; R_Axial_DIN0207_P10.16mm
R6: 20k; R_Axial_DIN0207_P10.16mm
TP1: 12 V; TestPoint_Keystone_5000
TP2: 5 V; TestPoint_Keystone_5000
TP3, TP4: GND; TestPoint_Keystone_5000
U1: ESP32 DevKit V1 (30 pinos); ESP32_DevKit_V1_30P_Socket
U2: SN65HVD230 (WCMCU-230, só escuta); SN65HVD230_Module_Socket
U3: RT8272 HW-108 (12 V → 5 V); RT8272_HW108_Socket

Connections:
3V3: R4.1, U1.15 (3V3), U2.1 (3V3), U2.3 (CTX)
5V: J3.4, J4.4, J5.4, TP2.1, U1.30 (VIN), U3.5 (OUT+)
12V: F1.1, J1.16 (+12V)
12V_FUS: F1.2, R5.1, TP1.1, U3.3 (IN+)
CANH: R4.2, U2.5 (CANH)
CANL: J1.14 (CAN-L), U2.6 (CANL)
CRX: U1.5 (D21), U2.4 (CRX)
GND: C1.2, J1.4 (GND_CH), J1.5 (GND_SIG), J3.3, J4.3, J5.3, R6.2, TP3.1, TP4.1, U1.14 (GND), U1.29 (GND), U2.2 (GND), U3.2 (IN-), U3.4 (OUT-)
LED_B: J6.5, U1.11 (D4)
LED_COM: J6.1, U1.7 (D18)
LED_G: J6.4, U1.10 (RX2)
LED_R: J6.3, U1.9 (TX2)
SCL: J3.2, J4.2, J5.2, U1.24 (D26)
SDA: J3.1, J4.1, J5.1, U1.23 (D25)
VBAT_ADC: C1.1, R5.2, R6.1, U1.19 (D34)

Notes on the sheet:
ALIMENTAÇÃO: OBD 16 (+12 V) → F1 1,5 A → RT8272 (5,0 V). OBD 4 e 5: GND.
CAN (só escuta): OBD 14 (CAN-L do painel) → CANL do SN65HVD230; CANH em 3,3 V por R4 (1 kΩ). O pino 6 do OBD fica sem ligação.
SN65HVD230 em 3,3 V: CRX direto no D21 do ESP32 (sem divisor). CTX preso no 3V3: o transceptor nunca transmite. Sem o R2 de 120 Ω do módulo.
Bateria: 12 V com fusível → R5 100 kΩ → D34 (ADC1) → R6 20 kΩ → GND, C1 100 nF de filtro. 12 V = 2,0 V no pino.
Sensores I2C (D25 = SDA, D26 = SCL), alimentados em 5 V (os módulos têm regulador): GY-273, LSM6DS3, BMP180.

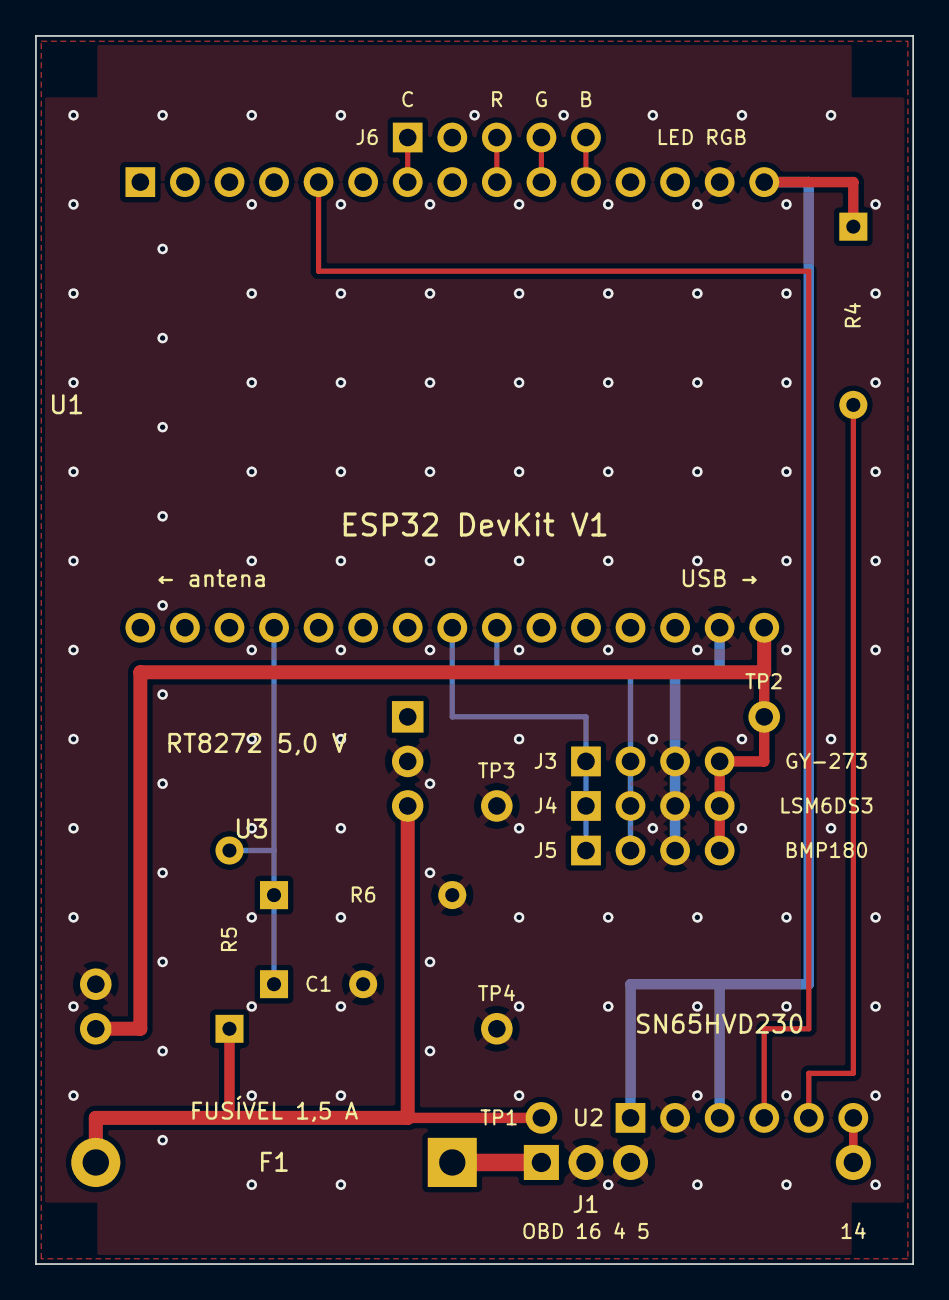
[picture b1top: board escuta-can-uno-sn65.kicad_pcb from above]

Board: 2 copper layers, 50.0 x 70.0 mm, 17 parts (0 on the bottom side), 15 nets.

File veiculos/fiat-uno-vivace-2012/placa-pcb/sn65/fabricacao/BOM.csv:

Comment,Designator,Footprint,Quantity,LCSC
100n,C1,C_Disc_D5.0mm_P5.08mm,1,
"1,5 A (vidro 5 x 20 mm)",F1,Fuseholder_AS06_5x20_P20.32,1,
"Cabo OBD2 macho (fios 16, 4, 5, 14)",J1,OBD_Pigtail_4W,1,
GY-273 (bússola),J3,PinHeader_1x04_H,1,
LSM6DS3 (acel./giro),J4,PinHeader_1x04_H,1,
BMP180 (pressão),J5,PinHeader_1x04_H,1,
LED tricolor (opcional),J6,PinHeader_1x05_H,1,
1k,R4,R_Axial_DIN0207_P10.16mm,1,
100k,R5,R_Axial_DIN0207_P10.16mm,1,
20k,R6,R_Axial_DIN0207_P10.16mm,1,
12 V,TP1,TestPoint_Keystone_5000,1,
5 V,TP2,TestPoint_Keystone_5000,1,
GND,"TP3,TP4",TestPoint_Keystone_5000,2,
ESP32 DevKit V1 (30 pinos),U1,ESP32_DevKit_V1_30P_Socket,1,
"SN65HVD230 (WCMCU-230, só escuta)",U2,SN65HVD230_Module_Socket,1,
RT8272 HW-108 (12 V → 5 V),U3,RT8272_HW108_Socket,1,

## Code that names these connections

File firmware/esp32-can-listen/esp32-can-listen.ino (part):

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const bool LED_RGB = true;           // false se não houver LED tricolor (os pinos ficam livres)
const bool LED_ANODO_COMUM = true;   // true: anodo comum (D18 em 3,3 V), o do projeto; false: catodo comum (D18 em 0 V)
const int LED_COMUM = 18;
const int LED_R = 17, LED_G = 16, LED_B = 4;
const unsigned long CAPTURA_MS = 1000;  // quadro mais recente que isso conta como "capturando"
const unsigned long PISCA_MS = 80;      // tempo aceso de cada piscada

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    pinMode(LED_COMUM, OUTPUT);
    gpio_set_drive_capability((gpio_num_t)LED_COMUM, GPIO_DRIVE_CAP_3);
    digitalWrite(LED_COMUM, LED_ANODO_COMUM ? HIGH : LOW);
    for (int pin : {LED_R, LED_G, LED_B}) {
      pinMode(pin, OUTPUT);
      // Corrente mínima (cerca de 5 mA): protege o LED e o pino se faltar o resistor
      gpio_set_drive_capability((gpio_num_t)pin, GPIO_DRIVE_CAP_0);
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
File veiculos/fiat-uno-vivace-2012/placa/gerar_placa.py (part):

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# ---------------------------------------------------------------- Versão alternativa: SN65HVD230 (WCMCU-230)
# Módulo de 15,7 x 13,9 mm, em 3,3 V: dispensa o divisor do RX (R1, R2, R3 e o J1 de antes). Barra de 6 pinos na linha 23,
# colunas 13 a 18 (3V3, GND, CTX, CRX, CANH, CANL), com o módulo deitado para cima, entre o BMP180 e o cabo OBD.
# CTX preso no 3V3 (trava física: nunca transmite), CRX direto no D21 pelo J1, CANH em 3,3 V pelo R4, CANL no pino 14.
# O R2 do módulo ("121", 120 ohms) fica ligado entre CANH e CANL: medido 120 ohms em 10/11/2026, ele sai (desenhado sem ele).
SN_MM = (15.7, 13.9)
SN_PINS = {}
TRANS_NOME = 'TJA1050'
if VARIANTE == 'sn65':
    TRANS_NOME = 'SN65HVD230'
    SN_PINS = {'3V3': (13, 23), 'GND': (14, 23), 'CTX': (15, 23), 'CRX': (16, 23), 'CANH': (17, 23), 'CANL': (18, 23)}
    TJA_PINS, TJA_CAN, CAN_HOLES = {}, {}, {}
    RES = [('R4', (16, 3), (16, 7), '3V3 → CANH')]
    TRACKS = [
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    ]
    JUMPERS = [
        ('J1', YEL, [(7, 3), (17, 3), (17, 21), (16, 21), (16, 22)], 'D21 → CRX do SN65HVD230 (fio direto, sem divisor)'),
        ('J2', BLU, [(16, 7), (18, 7), (18, 17)], 'R4 → CANH (segue por baixo até o pino CANH)'),
        ('J3', RED, [(2, 13), (9, 13), (9, 17), (10, 17)], 'OUT+ do RT8272 → 5 V'),
    ]
TRANS_PINS = SN_PINS or TJA_PINS
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            s.text(MX + 14.5 * P, MY + 19.6 * P, 'barra fêmea do SN65HVD230', 1.15, '#1565c0', bg=True)
        else:
            s.text(MX + 13.5 * P, MY + 19.5 * P, 'barra fêmea do TJA1050', 1.15, '#1565c0', bg=True)
            for n, (c, r) in CAN_HOLES.items():   # barra macho de 2 pinos: o conector dos fios do CANH e do CANL
                x, y = hp(c, r)
                s.add(f'<rect x="{x - 1.2:.2f}" y="{y - 1.2:.2f}" width="2.4" height="2.4" rx="0.3" fill="#455a64"/><rect x="{x - 0.4:.2f}" y="{y - 0.4:.2f}" width="0.8" height="0.8" fill="#d4af37"/>')
            s.text(hp(16.5, 24)[0], hp(16.5, 24)[1] - 1.9, 'CANH · CANL', 0.85, BLU, weight='bold', bg=True)
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    for name, col, pts, _ in BOTTOM_WIRES:
        jumper(s, pts, col, name, X=X)
    # nomes das trilhas
    labels = {'GND': (9, 19.5, BLK), '5 V': (13, 18, RED), 'RX': (14, 21, YEL), 'CAN-L': (17.5, 25.2, BLU), 'CANH': (18, 18.5, BLU), '12 V com fusível': (7.2, 20.5, PUR),
              'OUT+': (2, 18, RED), 'fusível': (FUSE_C[0], FUSE_C[1] + 1.3, PUR), '12 V': (10, 25.2, RED),
              'D21': (6.5, 1.0, YEL), '3V3': (16.5, 1.0, ORG), 'BMP180': (13.5, 17.9, CYA), 'D34': (5.9, 14.5, BAT)}
    if SN_PINS:
        labels.pop('RX')
        labels.update({'CANH': (18, 19.5, BLU), 'CAN-L': (18.6, 25.2, BLU), '3V3 ': (17, 15.5, ORG), 'CRX': (15.6, 21.6, YEL)})
    for t, (c, r, col) in labels.items():
        x, y = MX + (c - 1) * P, MY + (r - 1) * P
        s.text(X(x), y + 0.5, t, 1.25, col, weight='bold', bg=True)
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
